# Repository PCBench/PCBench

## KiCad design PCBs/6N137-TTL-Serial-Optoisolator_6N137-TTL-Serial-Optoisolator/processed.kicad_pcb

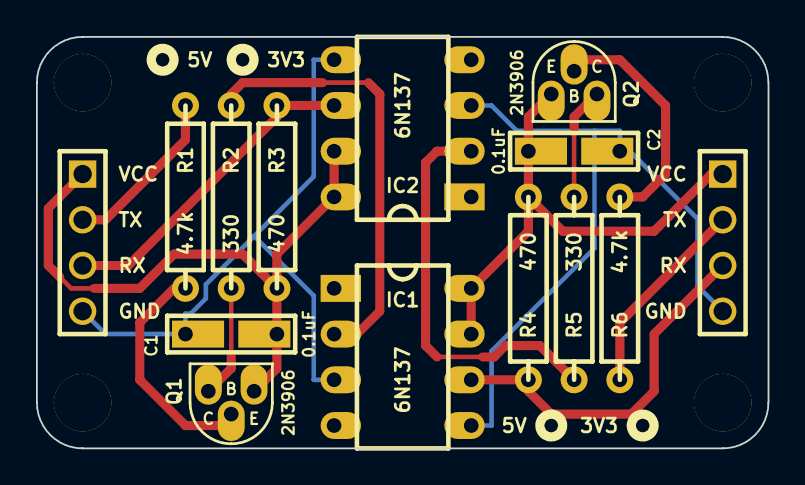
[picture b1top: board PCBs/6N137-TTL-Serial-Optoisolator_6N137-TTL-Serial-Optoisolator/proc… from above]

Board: 2 copper layers, 40.6 x 22.9 mm, 18 parts (0 on the bottom side), 14 nets.

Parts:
C1, C2: 0.1uF; CERCAP_2_059B_0805
H***: Val**; hole_M3_2
H***_2, H***_3, H***_4: Val**; hole_M3_2
IC1, IC2: 6N137; DIP8_059Bi_PL
P1, P2: CONN_4; PIN_ARRAY_4x1
Q1, Q2: 2N3906; TO-92_Q_EBC_059Bo_PL
R1, R6: 4.7k; R_AXIAL_0W25_059A_PL
R2, R5: 330; R_AXIAL_0W25_059A_PL
R3, R4: 470; R_AXIAL_0W25_059A_PL

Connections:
GNDA: C1.2, IC1.3, IC2.5, P1.4
GNDB: C2.2, IC1.5, IC2.3, P2.4
unnamed: Q2.2, R6.2
unnamed: Q1.2, R1.2
unnamed: Q1.3, R2.2
unnamed: Q2.3, R5.2
unnamed: IC1.2, R2.1
unnamed: IC2.2, R5.1
RXA: IC2.6, P1.3, R3.1
RXB: IC1.6, P2.3, R4.1
TXA: P1.2, R1.1
TXB: P2.2, R6.1
VCCA: C1.1, IC2.7, IC2.8, P1.1, Q1.1, R3.2
VCCB: C2.1, IC1.7, IC1.8, P2.1, Q2.1, R4.2

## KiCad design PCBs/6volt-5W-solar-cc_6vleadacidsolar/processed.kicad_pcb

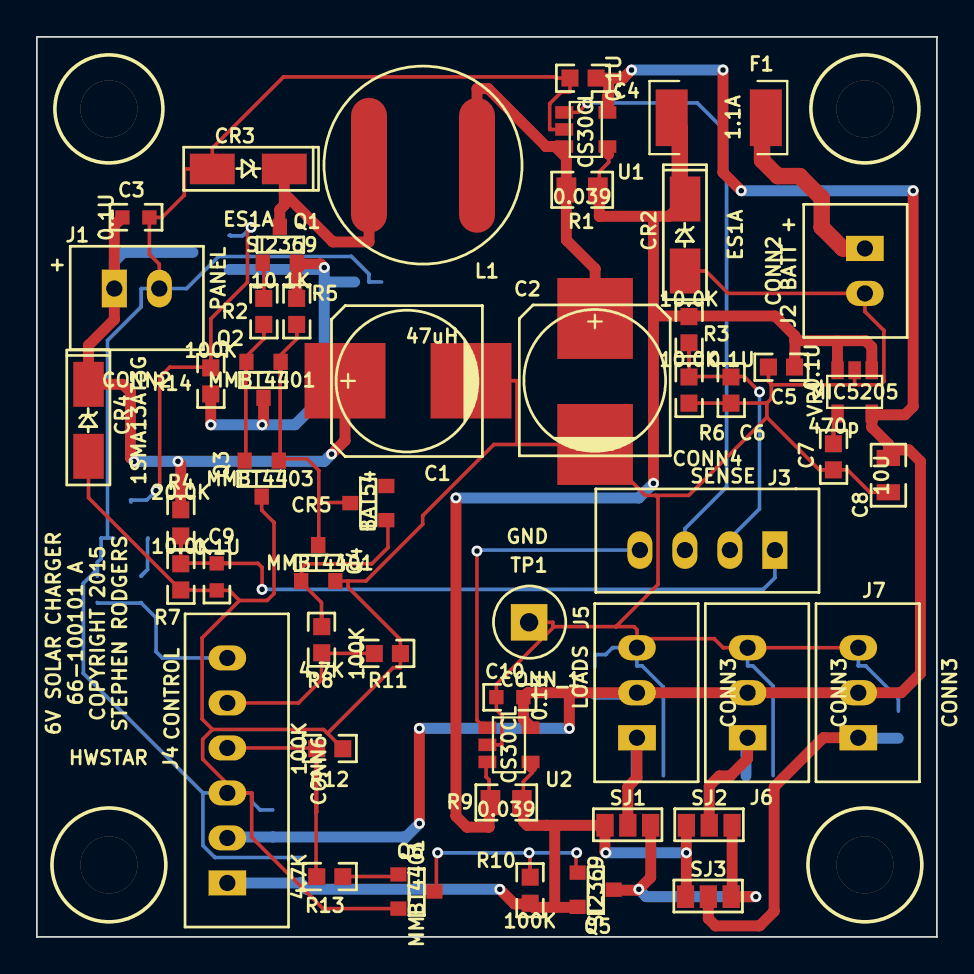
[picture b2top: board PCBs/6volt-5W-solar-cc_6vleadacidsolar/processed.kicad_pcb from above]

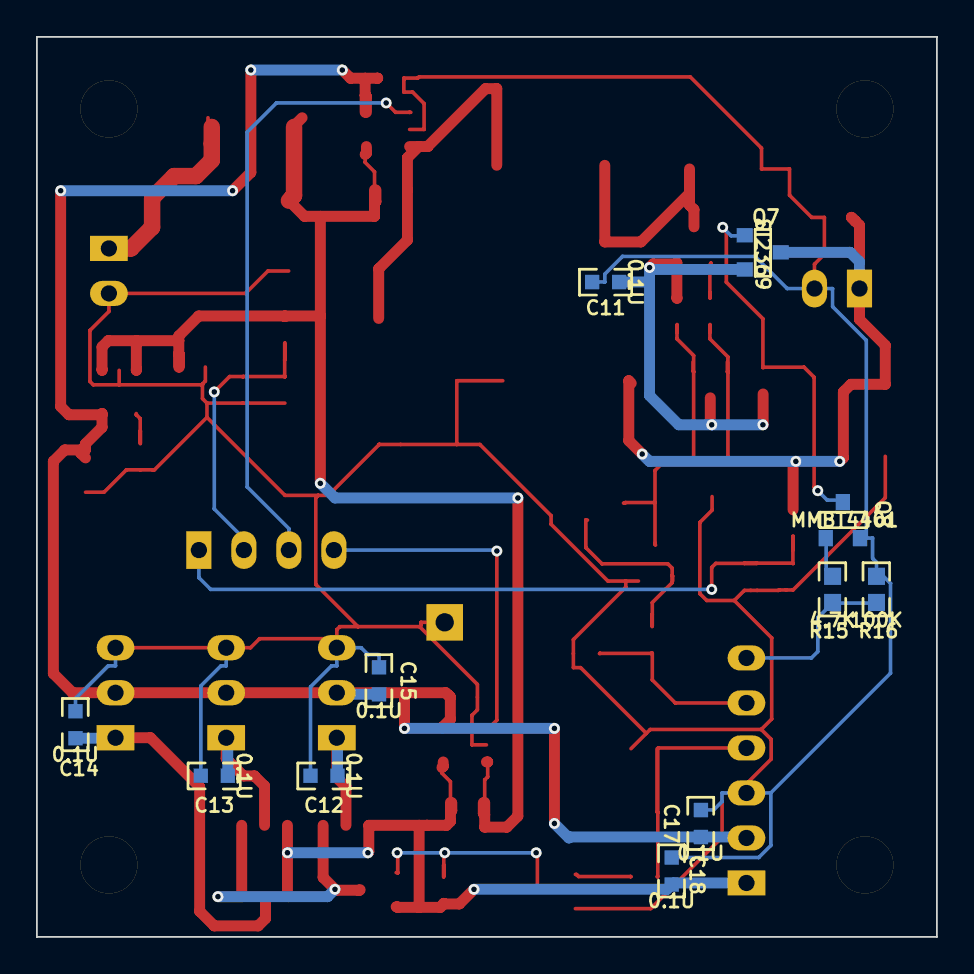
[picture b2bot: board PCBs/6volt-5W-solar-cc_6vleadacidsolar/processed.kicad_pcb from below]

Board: 2 copper layers, 50.0 x 50.0 mm, 65 parts (11 on the bottom side), 29 nets.

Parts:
C1, C2: 470U; CAP_ELEC_SMT_8X10
C3, C9, C10, C11, C12, C13, C14, C15, C17, C18: 0.1U; CC0603
C4, C5, C6: 0.1U; RC0603
C7: 470p; RC0603
C8: 10U; CC0805
CR2, CR3: ES1A; SMA-SAR
CR4: 1SMA13AT3G; SMA-SAR
CR5: BAT54; SOT23-3-SAR
F1: 1.1A; MINISMD1812
J1, J2: CONN2; JST_B2B_XH_A
J3: CONN4; JST_B4B_XH_A
J4: CONN6; JST_B6B_XH_A
J5, J6, J7: CONN3; JST_B3B_XH_A
L1: 47uH; BOURNS-SDE0805A
MTGHOLE125, MTGHOLE125_2, MTGHOLE125_3, MTGHOLE125_4: VAL**; MTGHOLE125
Q1, Q5, Q7: SI2369; SOT23-3-SAR
Q2, Q4, Q6, Q8: MMBT4401; SOT23-3-SAR
Q3: MMBT4403; SOT23-3-SAR
R1, R9: 0.039; RC0805
R2: 10; RC0603
R3, R6, R7: 10.0K; RC0603
R4: 20.0K; RC0603
R5: 1K; RC0603
R8, R13, R15: 4.7K; RC0603
R10, R11, R12, R14, R16: 100K; RC0603
SJ1, SJ2, SJ3: GS3; SJ3
TP1: CONN_1; TESTPIN
U1, U2: CS30CL; SOT23-5-SAR
VR1: MIC5205; SOT23-5-SAR

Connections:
+5V: C4.1, C8.1, C10.1, C15.1, C17.1, J4.2, J5.2, J6.2, J7.2, U1.5, U2.5, VR1.5
+BATT: C5.1, CR2.2, F1.1, R1.2, R3.1, R9.1, U1.4, U2.3, VR1.1, VR1.3
/CONVOUT: C2.1, L1.2, R1.1, U1.3
/ICONV: J3.3, U1.1
/ILOAD: J3.4, U2.1
/LOADEN: J4.4, R12.1, R13.1
/PV+: C1.1, C3.1, CR4.2, J1.1, Q7.3, R4.1
/PVEN: J4.6, R15.1, R16.1
/PVSW+: C11.1, Q1.2, Q2.3, Q7.2, R5.1, R14.2
/PWM: J4.5, R8.1, R11.1
/SWCONV: CR3.2, L1.1, Q1.3
/VBATT: C6.1, J3.2, R3.2, R6.1
/VPV: C9.1, J3.1, R4.2, R7.1
/VRAW: C18.1, J4.1, Q5.2, R9.2, R10.1, SJ1.1, SJ2.1, SJ3.1, U2.4
/VRAW1: C12.1, J5.1, SJ1.2
/VRAW2: C13.1, J6.1, SJ2.2
/VRAW3: C14.1, J7.1, SJ3.2
/VRAWSW: Q5.3, SJ1.3, SJ2.3, SJ3.3
GND: C1.2, C2.2, C3.2, C4.2, C5.2, C6.2, C7.2, C8.2, C9.2, C10.2, C11.2, C12.2, C13.2, C14.2, C15.2, C17.2, C18.2, CR2.1, CR3.1, CR4.1, J1.2, J2.2, J4.3, J5.3, J6.3, J7.3, Q3.3, Q4.2, Q6.2, Q8.2, R6.2, R7.2, R11.2, R12.2, R16.2, TP1.1, U1.2, U2.2, VR1.2
unnamed: C7.1, VR1.4
unnamed: CR5.1, Q4.1, R8.2
unnamed: CR5.3, Q2.1, Q3.1, Q4.3, R5.2
unnamed: F1.2, J2.1
unnamed: Q1.1, R2.1
unnamed: Q2.2, Q3.2, R2.2
unnamed: Q5.1, Q6.3, R10.2
unnamed: Q6.1, R13.2
unnamed: Q7.1, Q8.3, R14.1
unnamed: Q8.1, R15.2

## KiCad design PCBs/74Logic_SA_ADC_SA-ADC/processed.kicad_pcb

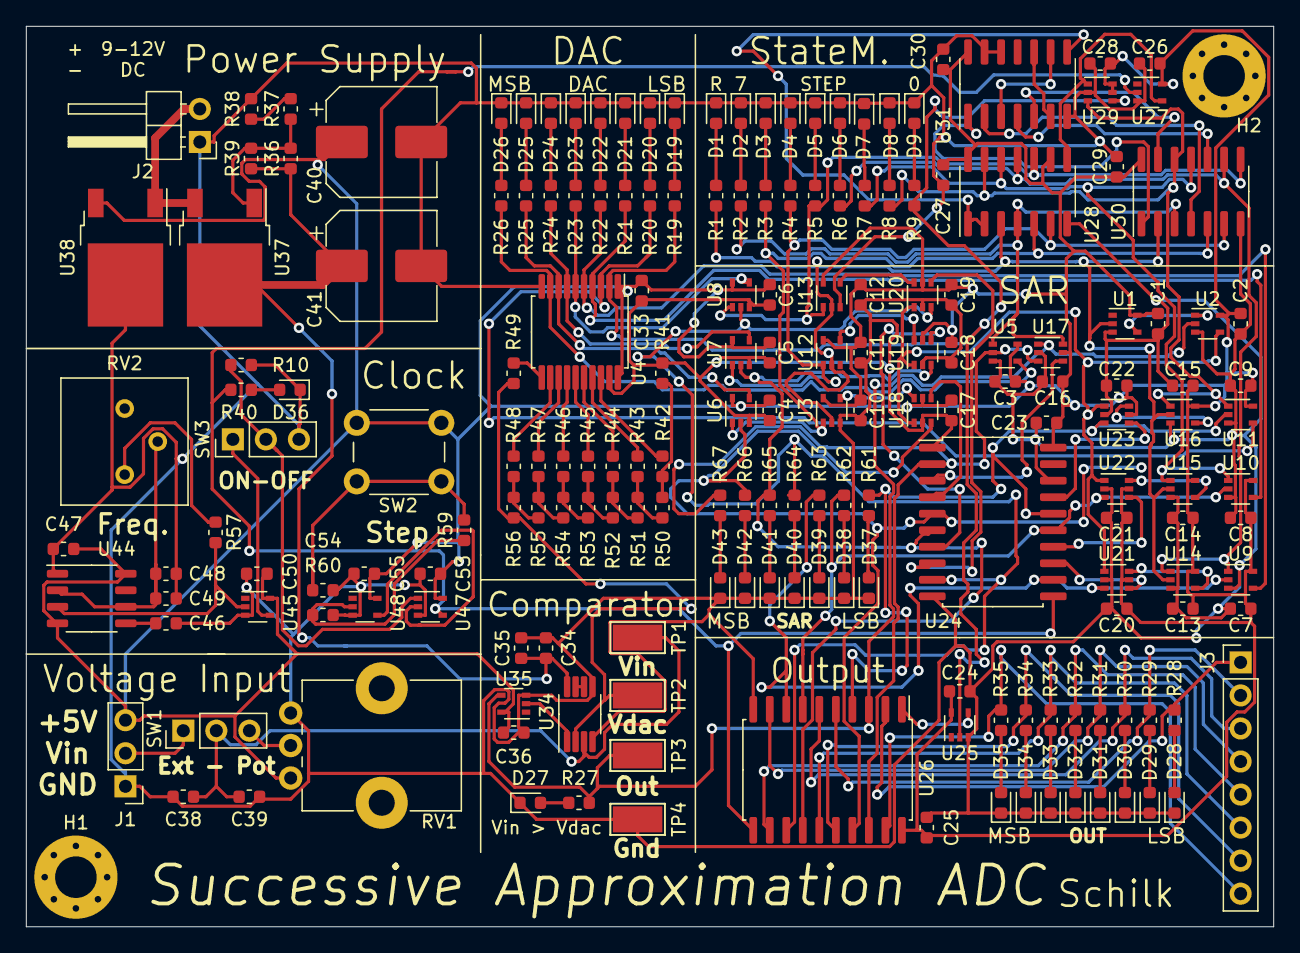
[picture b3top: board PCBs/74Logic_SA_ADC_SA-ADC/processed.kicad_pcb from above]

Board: 2 copper layers, 95.9 x 69.2 mm, 191 parts (0 on the bottom side), 127 nets.

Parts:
C1, C2, C3, C4, C5, C6, C7, C8, C9, C10, C11, C12, C13, C14, C15, C16, C17, C18, C19, C20, C21, C22, C23, C24, C25, C26, C27, C28, C29, C30, C33, C34, C36, C46, C47, C48, C50, C53, C54, C55: 0u1; C_0603_1608Metric
C35, C38, C39, C49: DNS; C_0603_1608Metric
C40, C41: 100u; CP_Elec_8x6.5
D1, D2, D3, D4, D5, D6, D7, D8, D9, D19, D20, D21, D22, D23, D24, D25, D26, D27, D28, D29, D30, D31, D32, D33, D34, D35, D36, D37, D38, D39, D40, D41, D42, D43: LED; LED_0603_1608Metric
H1, H2: MountingHole; MountingHole_3.2mm_M3_Pad_Via
J1: Vin; PinHeader_1x03_P2.54mm_Vertical
J2: Power; PinHeader_1x02_P2.54mm_Horizontal
J3: Out; PinHeader_1x08_P2.54mm_Vertical
R1, R2, R3, R4, R5, R6, R7, R8, R9, R19, R20, R21, R22, R23, R24, R25, R26, R27, R28, R29, R30, R31, R32, R33, R34, R35, R40, R61, R62, R63, R64, R65, R66, R67: 39K; R_0603_1608Metric
R10, R59, R60: 10K; R_0603_1608Metric
R36: 270R; R_0603_1608Metric
R37: 1K; R_0603_1608Metric
R38: 100R; R_0603_1608Metric
R39: DNS; R_0603_1608Metric
R41, R42, R43, R44, R45, R46, R47, R48, R49: 20K 0.1%; R_0603_1608Metric
R50, R51, R52, R53, R54, R55, R56: 10K 0.1%; R_0603_1608Metric
R57: 5K6; R_0603_1608Metric
RV1: 10K; Potentiometer_Alps_RK09K_Single_Vertical
RV2: 1Meg; Potentiometer_Bourns_3386P_Vertical
SW1, SW3: SW_Push_SPDT; PinHeader_1x03_P2.54mm_Vertical
SW2: SW_Push; SW_PUSH_6mm
TP1: Vin; TestPoint_Keystone_5019_Minature
TP2: Vdac; TestPoint_Keystone_5019_Minature
TP3: CompOut; TestPoint_Keystone_5019_Minature
TP4: GND; TestPoint_Keystone_5019_Minature
U1, U25, U27: SN74LVC1G04DCK; SOT-353_SC-70-5
U2: SN74LVC1G08DCK; SOT-353_SC-70-5
U3, U5, U6, U7, U8, U9, U10, U11, U12, U13, U14, U15, U16, U47: SN74LVC1G32DCK; SOT-353_SC-70-5
U4: SN74HC245DBR; SSOP-20_5.3x7.2mm_P0.65mm
U17, U18, U19, U20, U21, U22, U23: 74LVC1G157GW; SOT-363_SC-70-6
U24, U26: SN74HC377DW; SOIC-20W_7.5x12.8mm_P1.27mm
U28: 74HC161D; SOIC-14_3.9x8.7mm_P1.27mm
U29: SN74LVC1G175DCK; SOT-363_SC-70-6
U30: SN74HC02D; SOIC-14_3.9x8.7mm_P1.27mm
U31: SN74HC08D; SOIC-14_3.9x8.7mm_P1.27mm
U34: LM358ST; MSOP-8_3x3mm_P0.65mm
U35, U45, U48: 74LVC1G17DCK; SOT-353_SC-70-5
U37: LM317; TO-252-2
U38: L7805CDT; TO-252-2
U44: NE555DR; SOP-8_3.9x4.9mm_P1.27mm

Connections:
+5V: C1.1, C2.2, C3.2, C4.2, C5.2, C6.2, C7.2, C8.2, C9.2, C10.2, C11.2, C12.2, C13.2, C14.2, C15.2, C16.2, C17.2, C18.2, C19.2, C20.2, C21.2, C22.2, C23.2, C24.1, C25.2, C26.1, C27.1, C28.1, C29.1, C30.1, C33.2, C36.2, C40.1, C47.2, C50.2, C53.2, C55.2, J1.3, RV1.1, SW2.1, U1.5, U2.5, U3.5, U4.1, U4.20, U5.5, U6.5, U7.5, U8.5, U9.5, U10.5, U11.5, U12.5, U13.5, U14.5, U15.5, U16.5, U17.5, U18.5, U19.5, U20.5, U21.5, U22.5, U23.5, U24.20, U25.5, U26.20, U27.5, U28.9, U28.14, U29.5, U29.6, U30.14, U31.14, U35.5, U38.3, U44.4, U44.8, U45.5, U47.5, U48.5
/Analog/COMP_OUT: R27.2, TP3.1, U2.2, U17.1, U26.3, U35.4
/Analog/D0: R9.2, R19.2, U4.2, U25.2, U29.4
/Analog/D1: R20.2, U4.3, U11.4
/Analog/D2: R21.2, U4.4, U10.4
/Analog/D3: R22.2, U4.5, U9.4
/Analog/D4: R23.2, U4.6, U8.4
/Analog/D5: R24.2, U4.7, U7.4
/Analog/D6: R25.2, U4.8, U6.4
/Analog/D7: R26.2, U4.9, U5.4
/Analog/DAC/D0: R42.2, U4.18
/Analog/DAC/D1: R43.2, U4.17
/Analog/DAC/D2: R44.2, U4.16
/Analog/DAC/D3: R45.2, U4.15
/Analog/DAC/D4: R46.2, U4.14
/Analog/DAC/D5: R47.2, U4.13
/Analog/DAC/D6: R48.2, U4.12
/Analog/DAC/D7: R49.2, U4.11
/Analog/DAC/Vdac: R49.1, R56.1, TP2.1, U34.2
/Clock/CLK: R40.2, U24.11, U26.11, U27.2, U47.4
/Input/VIN: C38.1, C39.1, SW1.2, TP1.1, U34.3
/Output/OUT_1: R61.2, U11.2, U23.3, U24.16, U26.4
/Output/OUT_2: R62.2, U10.2, U22.3, U24.15, U26.7
/Output/OUT_3: R63.2, U9.2, U21.3, U24.12, U26.8
/Output/OUT_4: R64.2, U8.2, U20.3, U24.9, U26.13
/Output/OUT_5: R65.2, U7.2, U19.3, U24.6, U26.14
/Output/OUT_6: R66.2, U6.2, U18.3, U24.5, U26.17
/Output/OUT_7: R67.2, U5.2, U17.3, U24.2, U26.18
/SA-Register.sch/D: U2.4, U18.1, U19.1, U20.1, U21.1, U22.1, U23.1
/SA-Register.sch/STATE1: R8.2, U11.1, U16.1, U28.13, U29.3, U30.12
/SA-Register.sch/STATE2: R7.2, U10.1, U15.1, U28.12, U30.11
/SA-Register.sch/STATE3: R6.2, U9.1, U14.1, U28.11, U30.9
/SA-Register.sch/STATE4: R5.2, U8.1, U13.1, U28.10, U30.8
/SA-Register.sch/STATE5: R4.2, U7.1, U12.1, U28.6, U30.6
/SA-Register.sch/STATE6: R3.2, U3.1, U6.1, U28.5, U30.5
/SA-Register.sch/STATE7: R2.2, U5.1, U17.6, U28.4, U30.3
/SA-Register.sch/STATE_RST: R1.2, U1.2, U3.2, U12.2, U13.2, U14.2, U15.2, U16.2, U28.3, U30.2
/StateMaschine.sch/C_IN: U28.1, U28.2, U31.8
GND: C1.2, C2.1, C3.1, C4.1, C5.1, C6.1, C7.1, C8.1, C9.1, C10.1, C11.1, C12.1, C13.1, C14.1, C15.1, C16.1, C17.1, C18.1, C19.1, C20.1, C21.1, C22.1, C23.1, C24.2, C25.1, C26.2, C27.2, C28.2, C29.2, C30.2, C33.1, C34.2, C35.2, C36.1, C38.2, C39.2, C40.2, C41.2, C46.1, C47.1, C48.1, C49.1, C50.1, C53.1, C54.2, C55.1, D1.1, D2.1, D3.1, D4.1, D5.1, D6.1, D7.1, D8.1, D9.1, D19.1, D20.1, D21.1, D22.1, D23.1, D24.1, D25.1, D26.1, D27.1, D28.1, D29.1, D30.1, D31.1, D32.1, D33.1, D34.1, D35.1, D36.1, D37.1, D38.1, D39.1, D40.1, D41.1, D42.1, D43.1, J1.1, J2.1, R10.1, R38.2, R41.2, R60.2, RV1.3, SW3.3, TP4.1, U1.3, U2.3, U3.3, U4.10, U4.19, U5.3, U6.3, U7.3, U8.3, U9.3, U10.3, U11.3, U13.3, U14.3, U15.3, U16.3, U17.2, U18.2, U19.2, U20.2, U21.2, U22.2, U23.2, U24.1, U24.10, U24.18, U25.3, U26.10, U27.3, U28.7, U29.2, U30.7, U31.7, U31.12, U31.13, U34.4, U34.5, U35.3, U38.2, U44.1, U45.3, U47.3, U48.3
unnamed: C46.2, U44.5
unnamed: C48.2, C49.2, RV2.2, U44.2, U44.6
unnamed: C54.1, R59.1, U48.2
unnamed: D1.2, R1.1
unnamed: D2.2, R2.1
unnamed: D3.2, R3.1
unnamed: D4.2, R4.1
unnamed: D5.2, R5.1
unnamed: D6.2, R6.1
unnamed: D7.2, R7.1
unnamed: D8.2, R8.1
unnamed: D9.2, R9.1
unnamed: D19.2, R19.1
unnamed: D20.2, R20.1
unnamed: D21.2, R21.1
unnamed: D22.2, R22.1
unnamed: D23.2, R23.1
unnamed: D24.2, R24.1
unnamed: D25.2, R25.1
unnamed: D26.2, R26.1
unnamed: D27.2, R27.1
unnamed: D28.2, R28.1
unnamed: D29.2, R29.1
unnamed: D30.2, R30.1
unnamed: D31.2, R31.1
unnamed: D32.2, R32.1
unnamed: D33.2, R33.1
unnamed: D34.2, R34.1
unnamed: D35.2, R35.1
unnamed: D36.2, R40.1
unnamed: D37.2, R61.1
unnamed: D38.2, R62.1
unnamed: D39.2, R63.1
unnamed: D40.2, R64.1
unnamed: D41.2, R65.1
unnamed: D42.2, R66.1
unnamed: D43.2, R67.1
unnamed: J1.2, SW1.1
unnamed: J2.2, U37.3, U38.1
unnamed: J3.1, R28.2, U26.2
unnamed: J3.2, R29.2, U26.5
unnamed: J3.3, R30.2, U26.6
unnamed: J3.4, R31.2, U26.9
unnamed: J3.5, R32.2, U26.12
unnamed: J3.6, R33.2, U26.15
unnamed: J3.7, R34.2, U26.16
unnamed: J3.8, R35.2, U26.19
unnamed: R10.2, SW3.2, U47.1
unnamed: R36.2, R37.1, R39.2, U37.1
unnamed: R37.2, R38.1
unnamed: R41.1, R42.1, R50.1
unnamed: R43.1, R50.2, R51.2
unnamed: R44.1, R51.1, R52.2
unnamed: R45.1, R52.1, R53.2
unnamed: R46.1, R53.1, R54.2
unnamed: R47.1, R54.1, R55.2
unnamed: R48.1, R55.1, R56.2
unnamed: R57.1, RV2.1
unnamed: R57.2, U44.3, U45.2
unnamed: R59.2, R60.1, SW2.2
unnamed: RV1.2, SW1.3
unnamed: SW3.1, U45.4
unnamed: U1.4, U2.1
unnamed: U12.4, U19.6
unnamed: U13.4, U20.6
unnamed: U14.4, U21.6
unnamed: U15.4, U22.6
unnamed: U16.4, U23.6
unnamed: U17.4, U24.3
unnamed: U18.4, U24.4
unnamed: U3.4, U18.6
unnamed: U19.4, U24.7
unnamed: U20.4, U24.8
unnamed: U21.4, U24.13
unnamed: U22.4, U24.14
unnamed: U23.4, U24.17
unnamed: U25.4, U26.1
unnamed: U27.4, U28.8, U29.1
unnamed: U30.1, U31.1
unnamed: U30.4, U31.2
unnamed: U30.10, U31.4
unnamed: U30.13, U31.5
unnamed: U31.3, U31.9
unnamed: U31.6, U31.10
unnamed: U34.1, U35.2
unnamed: U34.6, U34.7
unnamed: U47.2, U48.4
VDDA: C34.1, C35.1, C41.1, R36.1, R39.1, U34.8, U37.2

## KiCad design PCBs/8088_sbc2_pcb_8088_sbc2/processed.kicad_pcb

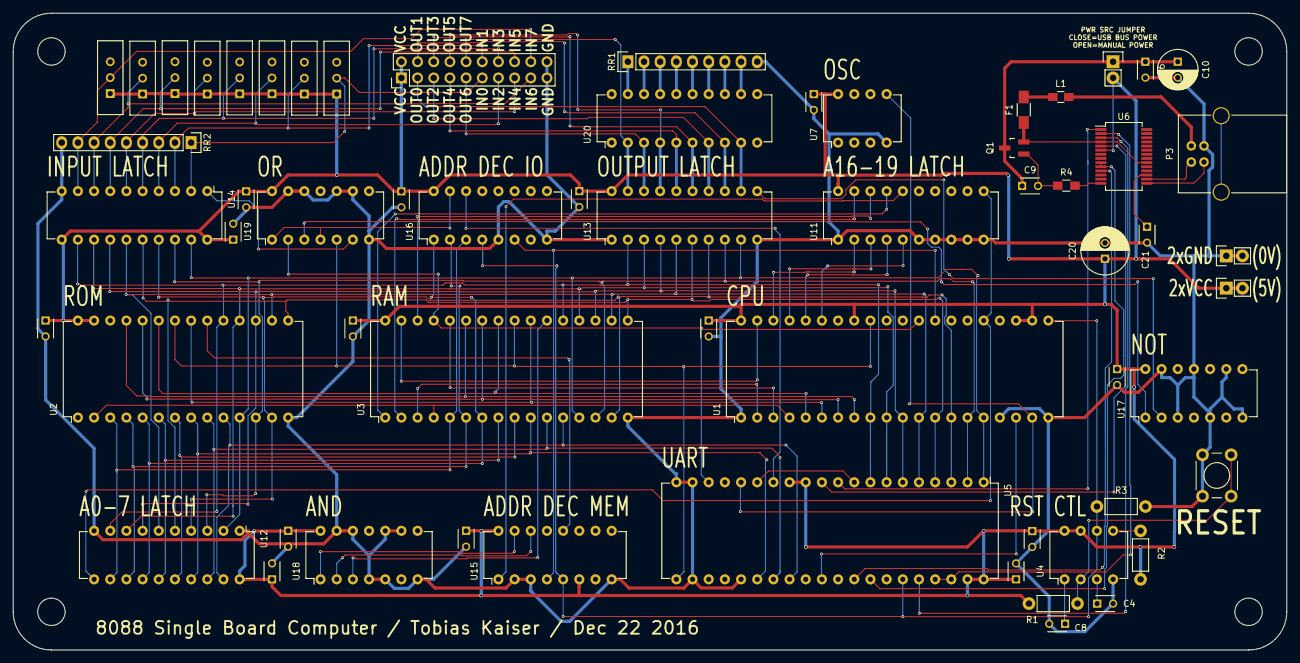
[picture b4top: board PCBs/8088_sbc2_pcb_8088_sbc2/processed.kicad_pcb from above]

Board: 2 copper layers, 200.0 x 100.0 mm, 61 parts (0 on the bottom side), 94 nets.

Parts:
C1, C2, C3, C4, C5, C6, C7, C8, C9, C11, C12, C13, C14, C15, C16, C17, C18, C19, C21: 100n; C_Disc_D3_P2.5
C10: 4u7; C_Radial_D6.3_L11.2_P2.5
C20: 4u7; C_Radial_D7.5_L11.2_P2.5
F1: FUSE; C_1206_HandSoldering
GND1: GND; Pin_Header_Straight_1x02
I0, I1, I2, I3, I4, I5, I6, I7: SWITCH_INV; EG1218
L1: INDUCTOR; C_0805_HandSoldering
P1: CONN_02X10; Pin_Header_Straight_2x10
P2: JMP_USB_PWR; Pin_Header_Straight_1x02
P3: USB_B
Q1: IRLML6402; SOT-23_Handsoldering
R1, R2, R3: 10k; Resistor_Horizontal_RM7mm
R4: 1K; R_0805_HandSoldering
RR1: 8x300R; Pin_Header_Straight_1x09
RR2: 8x10K; Pin_Header_Straight_1x09
SW1: SW_PUSH; SW_PUSH_6mm
U1: P8088; DIP-40_W15.24mm
U2: 28C64; DIP-28_W15.24mm
U3: AS6C4008; DIP-32_W15.24mm
U4: TL770xA; DIP-8_W7.62mm
U5: 16C550; DIP-40_W15.24mm
U6: FT232RL; SSOP-28_5.3x10.2mm_Pitch0.65mm
U7: OSC_SMALL; DIP-8_W7.62mm
U11, U12, U13, U14: 74HC573; DIP-20_W7.62mm
U15, U16: 74HC138; DIP-16_W7.62mm
U17: 74HC14_OWN; DIP-14_W7.62mm
U18: 74HC08; DIP-14_W7.62mm
U19: 74HC32; DIP-14_W7.62mm
U20: 10xLEDBAR; DIP-20_W7.62mm
VCC1: VCC; Pin_Header_Straight_1x02

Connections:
/A0: U2.10, U3.12, U5.28, U12.19
/A1: U2.9, U3.11, U5.27, U12.18
/A2: U2.8, U3.10, U5.26, U12.17
/A3: U2.7, U3.9, U12.16
/A4: U2.6, U3.8, U12.15
/A5: U2.5, U3.7, U12.14, U16.1
/A6: U2.4, U3.6, U12.13, U16.2
/A7: U2.3, U3.5, U12.12, U16.3
/A8: U1.8, U2.25, U3.27
/A9: U1.7, U2.24, U3.26
/A10: U1.6, U2.21, U3.23
/A11: U1.5, U2.23, U3.25
/A12: U1.4, U2.2, U3.4
/A13: U1.3, U3.28
/A14: U1.2, U3.3
/A15: U1.39, U3.31
/A16: U3.2, U11.19
/A17: U3.30, U11.18
/A18: U3.1, U11.17
/A19: U11.16, U15.1
/ALE: U1.25, U11.11, U12.11
/CLK: U1.19, U5.16, U7.5
/D0: U1.16, U2.11, U3.13, U5.1, U12.2, U13.9, U14.19
/D1: U1.15, U2.12, U3.14, U5.2, U12.3, U13.8, U14.18
/D2: U1.14, U2.13, U3.15, U5.3, U12.4, U13.7, U14.17
/D3: U1.13, U2.15, U3.17, U5.4, U12.5, U13.6, U14.16
/D4: U1.12, U2.16, U3.18, U5.5, U12.6, U13.5, U14.15
/D5: U1.11, U2.17, U3.19, U5.6, U12.7, U13.4, U14.14
/D6: U1.10, U2.18, U3.20, U5.7, U12.8, U13.3, U14.13
/D7: U1.9, U2.19, U3.21, U5.8, U12.9, U13.2, U14.12
/IN0: I0.2, P1.11, RR2.1, U14.2
/IN1: I1.2, P1.12, RR2.2, U14.3
/IN2: I2.2, P1.13, RR2.3, U14.4
/IN3: I3.2, P1.14, RR2.4, U14.5
/IN4: I4.2, P1.15, RR2.5, U14.6
/IN5: I5.2, P1.16, RR2.6, U14.7
/IN6: I6.2, P1.17, RR2.7, U14.8
/IN7: I7.2, P1.18, RR2.8, U14.9
/INTR: U1.18, U5.30
/IO/nM: U1.28, U15.4, U16.6
/IODEV0_WREN: U13.11, U17.2
/OUT0: P1.3, U13.12, U20.9
/OUT1: P1.4, U13.13, U20.8
/OUT2: P1.5, U13.14, U20.7
/OUT3: P1.6, U13.15, U20.6
/OUT4: P1.7, U13.16, U20.5
/OUT5: P1.8, U13.17, U20.4
/OUT6: P1.9, U13.18, U20.3
/OUT7: P1.10, U13.19, U20.2
/RES: R3.1, U1.21, U4.6, U5.35, U15.5, U16.4
/S3: U1.38, U11.2
/S4: U1.37, U11.3
/S5: U1.36, U11.4
/S6: U1.35, U11.5
/nIODEV0_EN: U16.15, U19.1, U19.4
/nIODEV0_RDEN: U14.1, U19.6
/nIODEV0_WREN: U17.1, U19.3
/nIODEV1_EN: U5.14, U16.14
/nRAMEN: U3.22, U18.3
/nRAMHIEN: U15.14, U18.2
/nRAMLOEN: U15.15, U18.1
/nRD: U1.32, U2.22, U3.24, U5.21, U19.5
/nRES: R2.2, U4.5
/nROMEN: U2.20, U15.12
/nWR: U1.29, U3.29, U5.18, U19.2
GND: C1.2, C2.2, C3.2, C4.2, C5.2, C6.2, C7.2, C8.2, C10.2, C11.2, C12.2, C13.2, C14.2, C15.2, C16.2, C17.2, C18.2, C19.2, C20.2, C21.2, GND1.1, GND1.2, P1.19, P1.20, P3.4, R3.2, RR1.9, RR2.9, SW1.1, U1.1, U1.17, U1.20, U2.14, U3.16, U4.4, U5.19, U5.20, U5.22, U5.25, U7.4, U11.1, U11.6, U11.7, U11.8, U11.9, U11.10, U12.1, U12.10, U13.1, U13.10, U14.10, U15.2, U15.3, U15.8, U16.5, U16.8, U17.3, U17.5, U17.7, U17.9, U17.11, U17.13, U18.4, U18.5, U18.7, U18.9, U18.10, U18.12, U18.13, U19.7, U19.9, U19.10, U19.12, U19.13
unnamed: C4.1, U4.3
unnamed: C8.1, U4.1
unnamed: C9.2, Q1.1, R4.1
unnamed: C6.1, C9.1, C10.1, P2.1, Q1.3
unnamed: C21.1, U6.17
unnamed: F1.1, Q1.2, U6.4, U6.20
unnamed: F1.2, L1.1
unnamed: L1.2, P3.1
unnamed: P3.2, U6.16
unnamed: P3.3, U6.15
unnamed: R1.2, SW1.2, U4.2
unnamed: R4.2, U6.14
unnamed: RR1.1, U20.19
unnamed: RR1.2, U20.18
unnamed: RR1.3, U20.17
unnamed: RR1.4, U20.16
unnamed: RR1.5, U20.15
unnamed: RR1.6, U20.14
unnamed: RR1.7, U20.13
unnamed: RR1.8, U20.12
unnamed: U5.10, U6.1
unnamed: U5.11, U6.5
unnamed: U5.9, U5.15
unnamed: U5.32, U6.11
unnamed: U5.33, U6.9, U6.10
unnamed: U5.36, U6.3
unnamed: U5.37, U5.38, U6.2
VCC: C1.1, C2.1, C3.1, C5.1, C7.1, C11.1, C12.1, C13.1, C14.1, C15.1, C16.1, C17.1, C18.1, C19.1, C20.1, I0.1, I1.1, I2.1, I3.1, I4.1, I5.1, I6.1, I7.1, P1.1, P1.2, P2.2, R1.1, R2.1, U1.22, U1.23, U1.33, U1.40, U2.27, U2.28, U3.32, U4.7, U4.8, U5.12, U5.13, U5.39, U5.40, U6.6, U7.8, U11.20, U12.20, U13.20, U14.11, U14.20, U15.6, U15.16, U16.16, U17.14, U18.14, U19.14, VCC1.1, VCC1.2

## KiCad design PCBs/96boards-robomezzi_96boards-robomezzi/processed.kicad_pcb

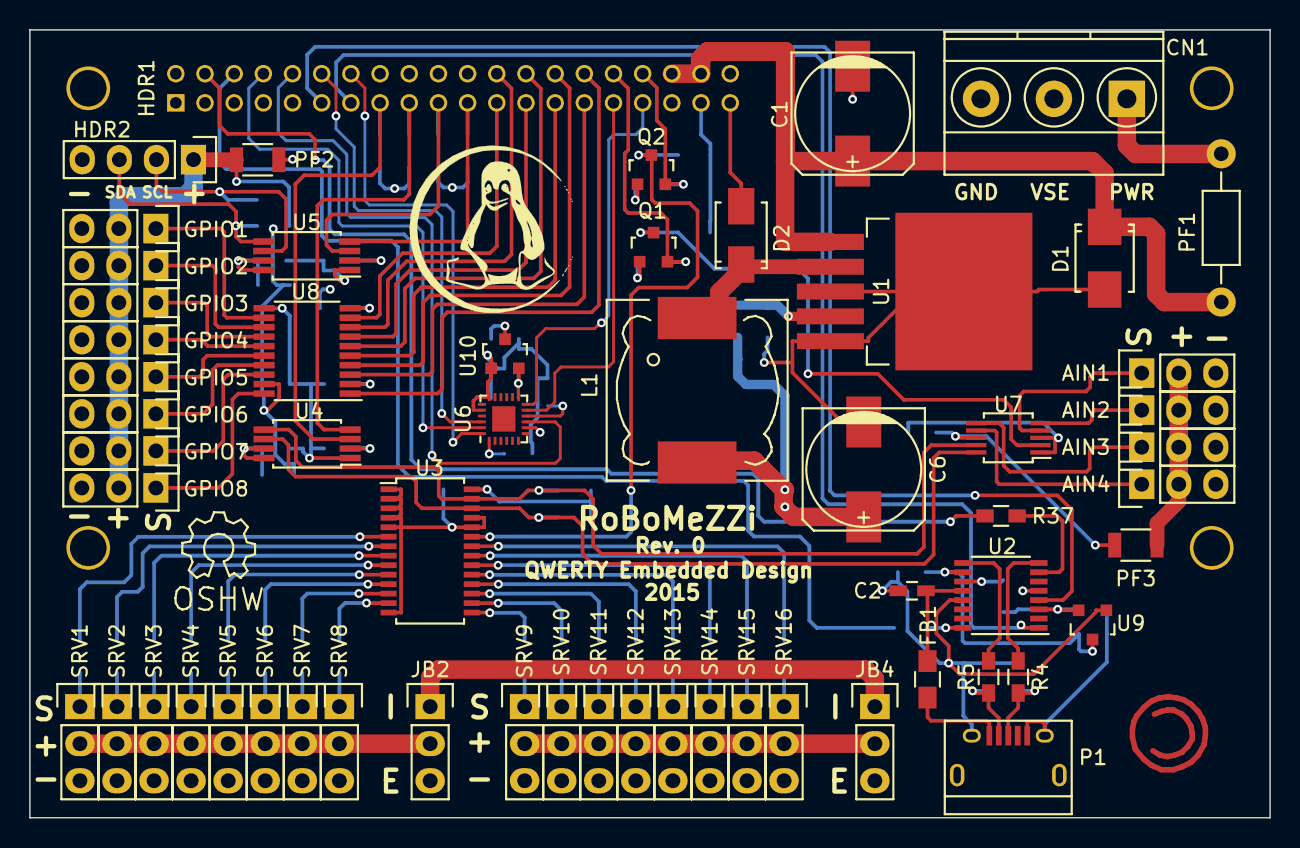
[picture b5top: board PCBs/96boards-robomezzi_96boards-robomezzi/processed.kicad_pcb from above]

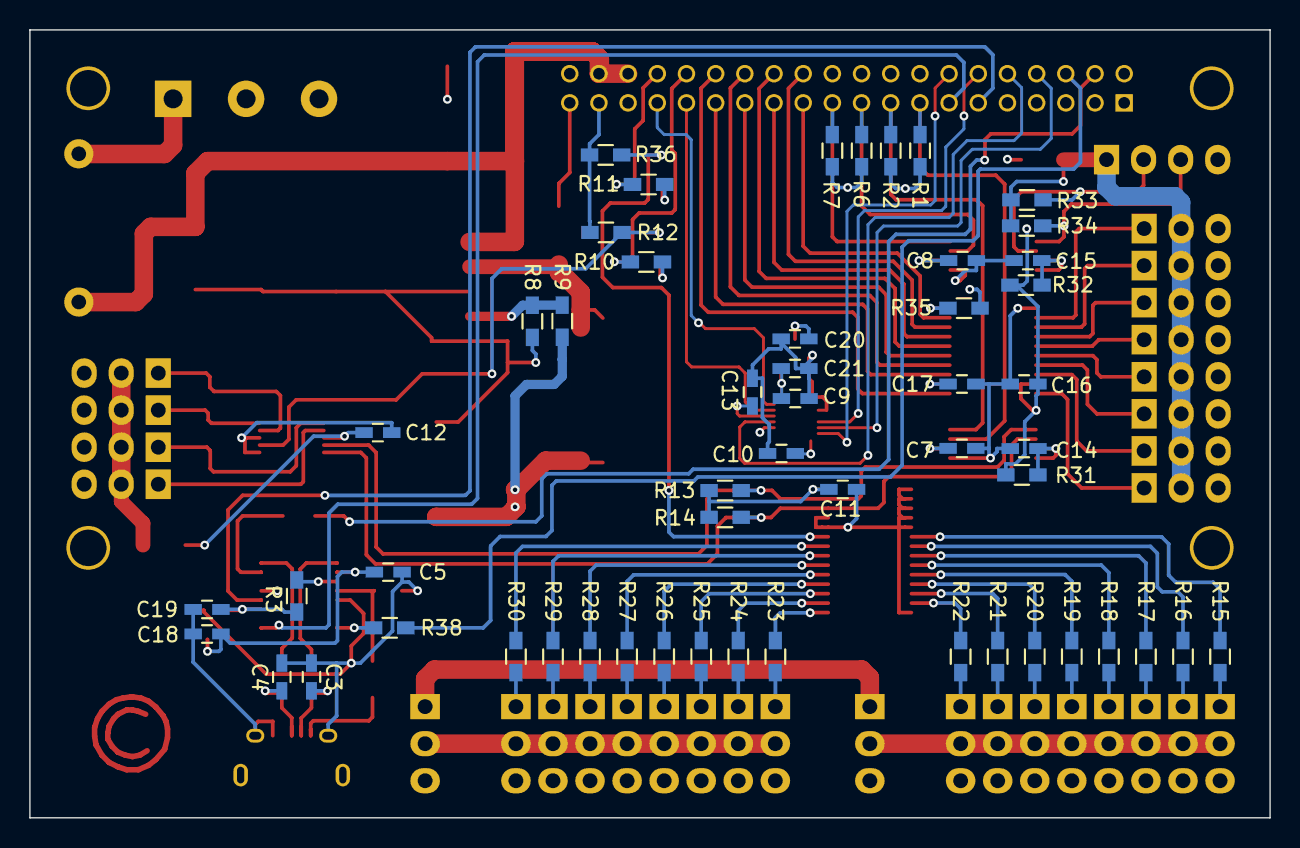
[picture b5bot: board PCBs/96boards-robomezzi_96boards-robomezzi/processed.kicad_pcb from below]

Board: 4 copper layers, 85.0 x 54.0 mm, 113 parts (53 on the bottom side), 103 nets.

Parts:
AIN1, AIN2, AIN3, AIN4: SRH3; Pin_Header_Straight_1x03
C1: 470 uF; c_elec_8x10.5
C2: 4.7uF; C_0603_HandSoldering
C3, C4: 47pF; C_0603_HandSoldering
C5, C7, C8, C9, C10, C11, C12, C13, C14, C15, C16, C17: .1uF; C_0603_HandSoldering
C6: 220 uF; c_elec_8x10.5
C18, C19, C20, C21: 10uF; C_0603_HandSoldering
CN1: PHOENIX3; TerminalBlock_Pheonix_MKDS1.5-3pol
D1: ZENER; SMB_Standard
D2: D_Schottky_Small; SMA_Standard
FB1: FILTER; C_0805_HandSoldering
GPIO1, GPIO2, GPIO3, GPIO4, GPIO5, GPIO6, GPIO7, GPIO8: SRH3; Pin_Header_Straight_1x03
HDR1: DRH40; dualrow2x20_2mm
HDR2: SRH4; Pin_Header_Straight_1x04
JB2, JB4: SRH3; Pin_Header_Straight_1x03
L1: 33 uH; Choke_SMD_12x12mm_h8mm
LOGO1: OPEN_HARDWARE_1; Symbol_OSHW-Logo_SilkScreen
P1: USB_OTG; USB_Micro-B
PF1: PF; Resistor_Horizontal_RM10mm
PF2, PF3: PF; R_1206
Q1, Q2: BSS138; SOT-23
R1, R2, R3, R6, R7, R10, R11, R12, R13, R14, R33, R34, R35, R36: 10K; R_0603_HandSoldering
R4, R5: 27; R_0603_HandSoldering
R8: 1K 1%; R_0603_HandSoldering
R9: 3.87K; R_0603_HandSoldering
R15, R16, R17, R18, R19, R20, R21, R22, R23, R24, R25, R26, R27, R28, R29, R30, R37, R38: 220; R_0603_HandSoldering
R31, R32: 200K; R_0603_HandSoldering
SRV1, SRV2, SRV3, SRV4, SRV5, SRV6, SRV7, SRV8, SRV9, SRV10, SRV11, SRV12, SRV13, SRV14, SRV15, SRV16: SRH3; Pin_Header_Straight_1x03
U1: LM2596S-ADJ; TO-263-5Lead
U2: FT230X; SSOP-16_3.9x4.9mm_Pitch0.635mm
U3: PCA9685; TSSOP-28_4.4x9.7mm_Pitch0.65mm
U4, U5: PCA9306; TSSOP-8_4.4x3mm_Pitch0.65mm
U6: MPU-9250; QFN-24-1EP_3x3mm_Pitch0.4mm
U7: ADS1015; MSOP-10_3x3mm_Pitch0.5mm
U8: TXS0108EPWR; TSSOP-20_4.4x6.5mm_Pitch0.65mm
U9: MCP1700T-1802E; SOT-23
U10: MCP1700T-3302E; SOT-23

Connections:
1V8: C7.1, C8.1, C10.1, C17.1, HDR1.35, Q1.1, Q2.1, R1.1, R2.1, R6.1, R7.1, R10.1, R11.1, R35.1, U4.2, U5.2, U6.1, U6.8, U8.2
1V8U: C19.1, R3.2, U2.3, U9.2
3P3U: C5.1, C18.1, U2.10, U9.3
3V3: C9.1, C21.1, U6.13, U10.2
5V: C11.1, C12.1, C16.1, C20.1, HDR1.37, PF2.2, PF3.2, R12.1, R13.1, R14.1, R31.2, R32.2, R36.1, U3.28, U7.8, U8.19, U10.3
5V_OUT: GPIO1.2, GPIO2.2, GPIO3.2, GPIO4.2, GPIO5.2, GPIO6.2, GPIO7.2, GPIO8.2, HDR2.1, PF2.1, R33.1, R34.1
96_I2C0_SCL: HDR1.15, R1.2, U4.3
96_I2C0_SDA: HDR1.17, R2.2, U4.4
96_I2C1_SCL: HDR1.19, R6.2, U5.3
96_I2C1_SDA: HDR1.21, R7.2, U5.4
96_UART1_RX: HDR1.13, U2.1
96_UART1_TX: HDR1.11, U2.4
ADC_RDY: Q1.3, R12.2, U7.2
AIN1: AIN1.1, U7.4
AIN2: AIN2.1, U7.5
AIN3: AIN3.1, U7.6
AIN4: AIN4.1, U7.7
GND: AIN1.3, AIN2.3, AIN3.3, AIN4.3, C1.2, C2.2, C3.2, C4.2, C5.2, C6.2, C7.2, C8.2, C9.2, C10.2, C11.2, C12.2, C13.2, C14.2, C15.2, C16.2, C17.2, C18.2, C19.2, C20.2, C21.2, CN1.3, D1.2, D2.2, GPIO1.3, GPIO2.3, GPIO3.3, GPIO4.3, GPIO5.3, GPIO6.3, GPIO7.3, GPIO8.3, HDR1.1, HDR1.2, HDR1.39, HDR1.40, HDR2.4, P1.5, P1.6, R8.2, SRV1.3, SRV2.3, SRV3.3, SRV4.3, SRV5.3, SRV6.3, SRV7.3, SRV8.3, SRV9.3, SRV10.3, SRV11.3, SRV12.3, SRV13.3, SRV14.3, SRV15.3, SRV16.3, U1.3, U1.5, U2.5, U2.13, U3.1, U3.2, U3.3, U3.4, U3.5, U3.14, U3.24, U3.25, U4.1, U5.1, U6.18, U6.20, U7.1, U7.3, U8.11, U9.1, U10.1
GPIO1: HDR1.23, U8.9
GPIO1_5V: GPIO1.1, U8.12
GPIO2: HDR1.24, U8.8
GPIO2_5V: GPIO2.1, U8.13
GPIO3: HDR1.25, U8.7
GPIO3_5V: GPIO3.1, U8.14
GPIO4: HDR1.26, U8.6
GPIO4_5V: GPIO4.1, U8.15
GPIO5: HDR1.27, U8.5
GPIO5_5V: GPIO5.1, U8.16
GPIO6: HDR1.28, U8.4
GPIO6_5V: GPIO6.1, U8.17
GPIO7: HDR1.29, U8.3
GPIO7_5V: GPIO7.1, U8.18
GPIO8: HDR1.30, U8.1
GPIO8_5V: GPIO8.1, U8.20
I2C0_SCL: R14.2, U3.26, U4.6, U7.10
I2C0_SDA: R13.2, U3.27, U4.5, U7.9
I2C1_SCL: HDR2.2, R33.2, U5.6
I2C1_SDA: HDR2.3, R34.2, U5.5
MPU_FSYNC: HDR1.31, U6.11
MPU_INT: HDR1.33, U6.12
unnamed: AIN1.2, AIN2.2, AIN3.2, AIN4.2, PF3.1
unnamed: C2.1, FB1.1, U2.12
unnamed: C3.1, P1.2, R5.2
unnamed: C4.1, P1.3, R4.2
unnamed: C13.1, U6.10
unnamed: C14.1, R31.1, U4.7, U4.8
unnamed: C15.1, R32.1, U5.7, U5.8
unnamed: CN1.1, PF1.2
unnamed: D2.1, L1.1, U1.2
unnamed: FB1.2, P1.1
unnamed: HDR1.32, Q1.2, R10.2
unnamed: HDR1.34, Q2.2, R11.2
unnamed: R3.1, U2.11
unnamed: R4.1, U2.8
unnamed: R5.1, U2.9
unnamed: R8.1, R9.1, U1.4
unnamed: R15.2, U3.6
unnamed: R16.2, U3.7
unnamed: R17.2, U3.8
unnamed: R18.2, U3.9
unnamed: R19.2, U3.10
unnamed: R20.2, U3.11
unnamed: R21.2, U3.12
unnamed: R22.2, U3.13
unnamed: R23.2, U3.15
unnamed: R24.2, U3.16
unnamed: R25.2, U3.17
unnamed: R26.2, U3.18
unnamed: R27.2, U3.19
unnamed: R28.2, U3.20
unnamed: R29.2, U3.21
unnamed: R30.2, U3.22
unnamed: R35.2, U8.10
unnamed: R37.1, U2.7
unnamed: R38.1, U2.16
PWR_BTN: HDR1.4, R37.2
RST_BTN: HDR1.6, R38.2
SERVO1: R15.1, SRV1.1
SERVO2: R16.1, SRV2.1
SERVO3: R17.1, SRV3.1
SERVO4: R18.1, SRV4.1
SERVO5: R19.1, SRV5.1
SERVO6: R20.1, SRV6.1
SERVO7: R21.1, SRV7.1
SERVO8: R22.1, SRV8.1
SERVO9: R23.1, SRV9.1
SERVO10: R24.1, SRV10.1
SERVO11: R25.1, SRV11.1
SERVO12: R26.1, SRV12.1
SERVO13: R27.1, SRV13.1
SERVO14: R28.1, SRV14.1
SERVO15: R29.1, SRV15.1
SERVO16: R30.1, SRV16.1
SERVO_NOE: Q2.3, R36.2, U3.23
SPI0_CSN: HDR1.12, U6.22
SPI0_MISO: HDR1.10, U6.9
SPI0_MOSI: HDR1.14, U6.24
SPI0_SCLK: HDR1.8, U6.23
VBAT: C1.1, D1.1, HDR1.36, HDR1.38, PF1.1, U1.1
VSERVOB1: JB2.2, SRV1.2, SRV2.2, SRV3.2, SRV4.2, SRV5.2, SRV6.2, SRV7.2, SRV8.2
VSERVOB2: JB4.2, SRV9.2, SRV10.2, SRV11.2, SRV12.2, SRV13.2, SRV14.2, SRV15.2, SRV16.2
VSERVOE: CN1.2, JB2.3, JB4.3
VSERVOI: C6.1, JB2.1, JB4.1, L1.2, R9.2

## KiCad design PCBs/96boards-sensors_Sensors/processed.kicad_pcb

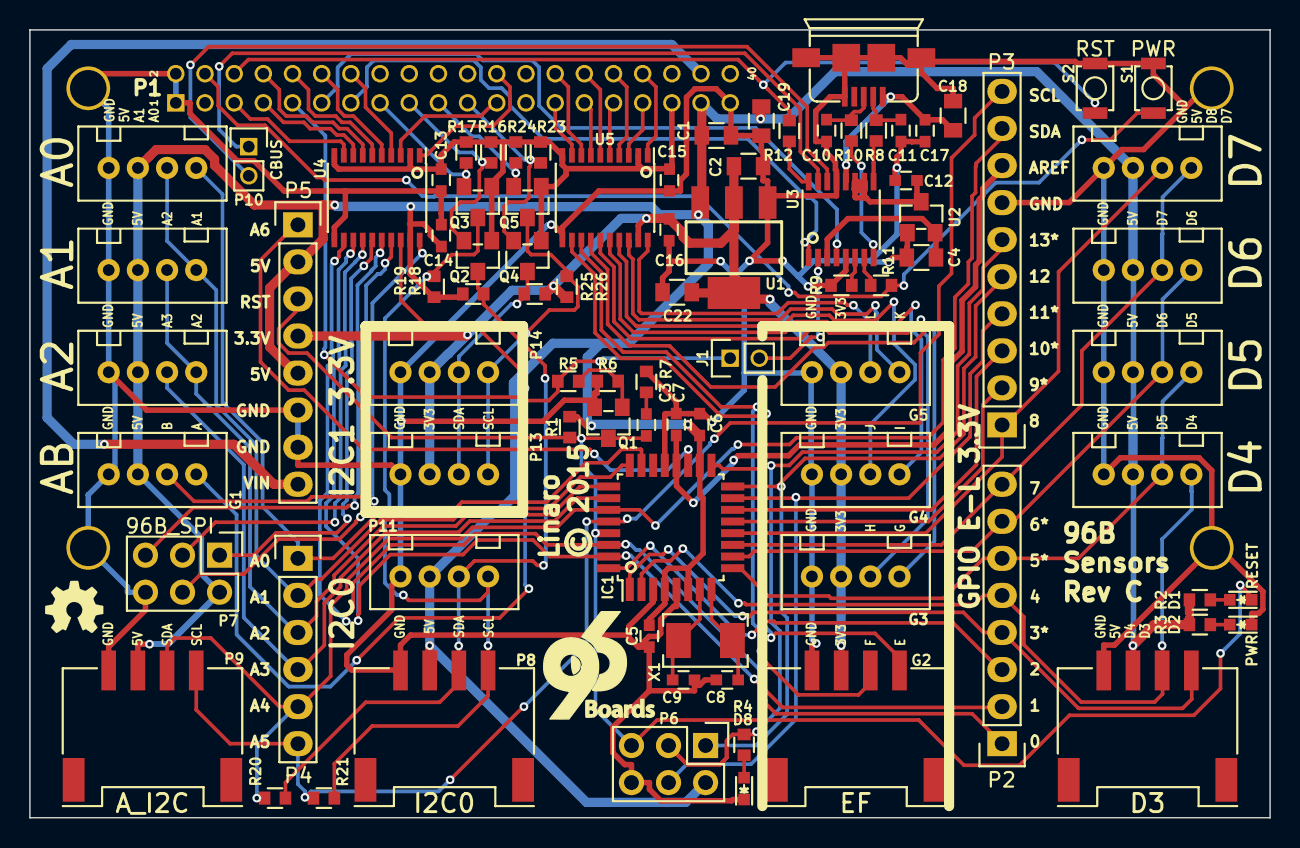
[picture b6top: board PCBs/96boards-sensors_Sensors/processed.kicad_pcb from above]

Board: 2 copper layers, 85.0 x 54.0 mm, 87 parts (0 on the bottom side), 91 nets.

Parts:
A0, A1, A2: GROVE; Grove4P
C1, C2, C4: 2u2; C_0805
C3, C5, C6, C7, C12, C13, C14, C15, C16, C17: 100n; C_0603
C8, C9: 22p; C_0603
C10, C11: 39p; C_0603
C18, C19, C22: 10u; C_0805
CON1: CONSOLE; USB_MICRO_B_ST-USB-001E
D1: RESET; LED-0603
D2: PWR; LED-0603
D3: GROVE; Grove_SMD_Connector
D4, D5, D6, D7: GROVE; Grove4P
D8: PB5; LED-0603
G1: AB; Grove4P
G2: EF; Grove_SMD_Connector
G3: GH; Grove4P
G4: IJ; Grove4P
G5: KL; Grove4P
IC1: ATMEGA328P; TQFP-32_7x7mm_Pitch0.8mm
J1: RST_TEST; Pin_Header_Straight_1x02_Pitch2mm
P1: CONN_02X20; 96Boards_LS_EXP
P2, P5: CONN_01X08; Socket_Strip_Straight_1x08
P3: CONN_01X10; Socket_Strip_Straight_1x10
P4: CONN_01X06; Socket_Strip_Straight_1x06
P6: AVR_SPI; Pin_Header_Straight_2x03
P7: 96B_SPI; Pin_Header_Straight_2x03
P8: I2C0; Grove_SMD_Connector
P9: A_I2C; Grove_SMD_Connector
P10: CBUS; Pin_Header_Straight_1x02_Pitch2mm
P11: I2C0; Grove4P
P13, P14: I2C1; Grove4P
Q1: S8050; SOT-23_Seeed
Q2, Q3, Q4, Q5: BSS138; SOT-23_Seeed
R1, R6, R9, R16, R17, R18, R19, R23, R24, R25, R26: 10K; R_0603_Seeed
R2, R3, R4: 1K; R_0603_Seeed
R5, R7: 620R; R_0603_Seeed
R8, R10: 22R; R_0603_Seeed
R11, R12: 220R; R_0603_Seeed
R20, R21: R; R_0603_Seeed
S1: PWR; SW_PUSH_B3U_1000P
S2: RST; SW_PUSH_B3U_1000P
U1: CJT1117-3.3; SOT223
U2: XC6206; SOT-23_Seeed
U3: FT230XS; SSOP-16_3.9x4.9mm_Pitch0.635mm
U4: TXB0108PW; SSOP-20_4.4x6.5mm_Pitch0.65mm
U5: TXS0108E; SSOP-20_4.4x6.5mm_Pitch0.65mm
X1: 16MHz; Crystal_3.2X5_SMD

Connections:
96UART0_RTS: J1.1, P1.9, R5.2
96UART0_RX: P1.7, U4.8
96UART0_TX: P1.5, U4.9
96UART1_RX: P1.13, U3.1
96UART1_TX: P1.11, U3.4
+1V8: C13.1, C15.1, P1.35, Q2.1, Q3.1, Q4.1, Q5.1, R16.1, R17.1, R23.1, R24.1, U4.2, U4.10, U5.2, U5.10
+1V8F: C4.1, U2.2, U3.3
+3V3: C2.1, C16.1, C22.1, G2.3, G3.3, G4.3, G5.3, P5.4, P13.3, P14.3, R25.1, R26.1, U1.2, U5.19
+3V3F: C12.1, U2.3, U3.10, U3.11
+5V: A0.3, A1.3, A2.3, C1.1, C5.1, C6.1, C14.1, C19.1, D3.3, D4.3, D5.3, D6.3, D7.3, G1.3, IC1.4, IC1.6, IC1.18, P1.37, P5.2, P5.5, P6.2, P7.2, P8.3, P9.3, P11.3, R1.1, R2.1, R3.1, R18.1, R19.1, U1.3, U4.19
/+5F: C17.1, C18.1, CON1.1, U3.12
/USBDM: C11.1, CON1.2, R8.2
/USBDP: C10.1, CON1.3, R10.2
ADC6: IC1.19, P5.1
AREF: C7.1, IC1.20, P3.8
GND: A0.4, A1.4, A2.4, C1.2, C2.2, C4.2, C5.2, C6.2, C7.2, C8.2, C9.2, C10.2, C11.2, C12.2, C13.2, C14.2, C15.2, C16.2, C17.2, C18.2, C19.2, C22.2, CON1.5, CON1.6, CON1.7, CON1.8, CON1.9, D2.1, D3.4, D4.4, D5.4, D6.4, D7.4, D8.1, G1.4, G2.4, G3.4, G4.4, G5.4, IC1.3, IC1.5, IC1.21, P1.1, P1.2, P1.39, P3.7, P5.6, P5.7, P6.6, P7.6, P8.4, P9.4, P11.4, P13.4, P14.4, Q1.2, R6.1, R7.2, R9.1, S1.2, S2.2, U1.1, U2.1, U3.5, U3.13, U4.11, U5.11
GPIO_A: P1.23, U4.3
GPIO_A_5: G1.1, U4.18
GPIO_B: P1.24, U4.1
GPIO_B_5: G1.2, U4.20
GPIO_E: P1.27, U5.9
GPIO_E_3: G2.1, U5.12
GPIO_F: P1.28, U5.8
GPIO_F_3: G2.2, U5.13
GPIO_G: P1.29, U5.7
GPIO_G_3: G3.1, U5.14
GPIO_H: P1.30, U5.6
GPIO_H_3: G3.2, U5.15
GPIO_I: P1.31, U5.5
GPIO_I_3: G4.1, U5.16
GPIO_J: P1.32, U5.4
GPIO_J_3: G4.2, U5.17
GPIO_K: P1.33, U5.3
GPIO_K_3: G5.1, U5.18
GPIO_L: P1.34, U5.1
GPIO_L_3: G5.2, U5.20
I2C0_SCL: P1.15, Q3.2, R17.2
I2C0_SCL_5: P8.1, P11.1, Q3.3, R19.2, R21.2
I2C0_SDA: P1.17, Q2.2, R16.2
I2C0_SDA_5: P8.2, P11.2, Q2.3, R18.2, R20.2
I2C1_SCL: P1.19, Q5.2, R24.2
I2C1_SCL_3: P13.1, P14.1, Q5.3, R26.2
I2C1_SDA: P1.21, Q4.2, R23.2
I2C1_SDA_3: P13.2, P14.2, Q4.3, R25.2
unnamed: C3.2, R7.1
unnamed: C8.1, IC1.8, X1.1
unnamed: C9.1, IC1.7, X1.2
unnamed: D1.2, R2.2
unnamed: D2.2, R3.2
unnamed: D8.2, R4.2
unnamed: P10.1, U3.15
unnamed: P10.2, U3.14
unnamed: Q1.1, R5.1, R6.2
unnamed: R8.1, U3.9
unnamed: R9.2, U3.6
unnamed: R10.1, U3.8
unnamed: R11.2, U3.7
unnamed: R12.2, U3.16
PB0: D7.2, IC1.12, P3.1
PB1: IC1.13, P3.2
PB2: IC1.14, P3.3
PB3_MOSI: IC1.15, P3.4, P6.4
PB4_MISO: IC1.16, P3.5, P6.1
PB5_SCK: IC1.17, P3.6, P6.3, R4.1
PC0: A0.1, IC1.23, P4.1
PC1: A0.2, A1.1, IC1.24, P4.2
PC2: A1.2, A2.1, IC1.25, P4.3
PC3: A2.2, IC1.26, P4.4
PC4_SDA: IC1.27, P3.9, P4.5, P9.2, R20.1
PC5_SCL: IC1.28, P3.10, P4.6, P9.1, R21.1
PD0_RX: IC1.30, P2.1, U4.12
PD1_TX: IC1.31, P2.2, U4.13
PD2_INT0: IC1.32, P2.3
PD3_INT1: D3.1, IC1.1, P2.4
PD4: D3.2, D4.1, IC1.2, P2.5
PD5: D4.2, D5.1, IC1.9, P2.6
PD6: D5.2, D6.1, IC1.10, P2.7
PD7: D6.2, D7.1, IC1.11, P2.8
PWR_BTN: P1.4, R11.1, S1.1
PWR_IN: P1.38, P5.8
RESET: C3.1, D1.1, IC1.29, P5.3, P6.5, Q1.3, R1.2
RST_BTN: P1.6, R12.1, S2.1
SPI0_CS: P1.12, U4.5
SPI0_CS_5: P7.5, U4.16
SPI0_MISO: P1.10, U4.6
SPI0_MISO_5: P7.1, U4.15
SPI0_MOSI: P1.14, U4.4
SPI0_MOSI_5: P7.4, U4.17
SPI0_SCK: P1.8, U4.7
SPI0_SCK_5: P7.3, U4.14
TEST_RESET: J1.2, U3.2

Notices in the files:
PCBs/6volt-5W-solar-cc_6vleadacidsolar/processed.kicad_pcb:
COPYRIGHT 2015
PCBs/96boards-sensors_Sensors/processed.kicad_pcb:
© 2015
